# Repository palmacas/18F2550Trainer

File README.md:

# PIC18F2550 Trainer

Small PCB based on a PIC18F2550, with USB connectivity. All the GPIO pins are exposed to headers. The board includes ICSP connector for programming, but the microcontroller also can be programmed with a bootloader.

---
More information:\
[PIC18F2550 Trainer [Spanish]](https://palmacas.com/pic18f2550-trainer/)

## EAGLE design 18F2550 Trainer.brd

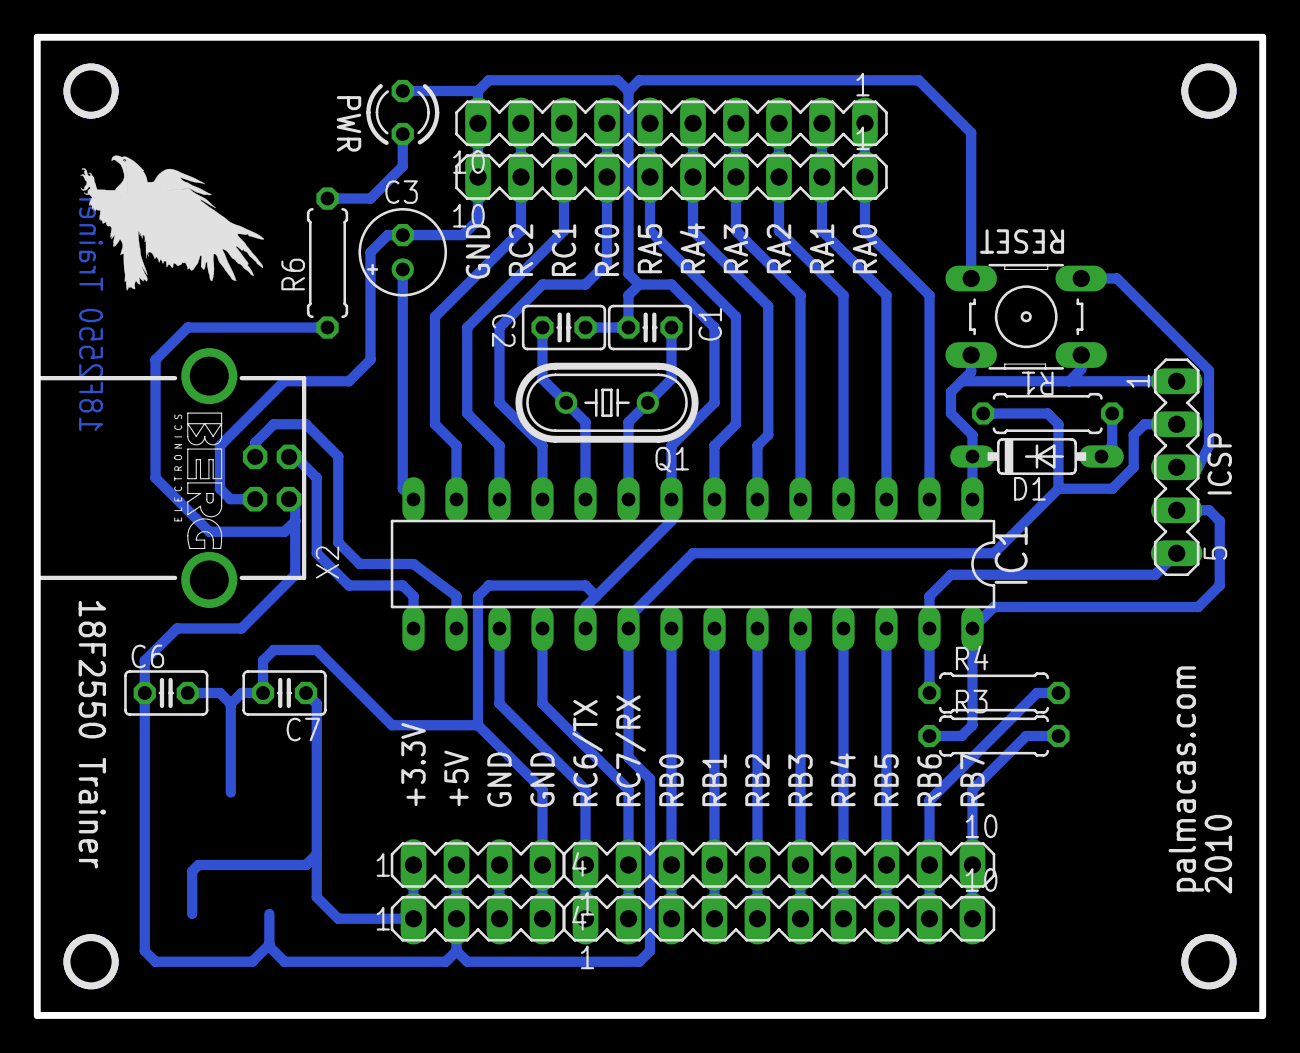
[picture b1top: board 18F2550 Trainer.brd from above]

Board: 2 copper layers, 72.4 x 57.8 mm, 25 parts (1 on the bottom side), 32 nets.

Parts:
C1, C2: 22pF; C025-025X050
C3: 47uF; E2-5
C6, C7: 1uF; C025-025X050
D1: 1N4148DO35-7; DO35-7
IC1: PIC18F2550_28DIP; DIL28-3
IC2: UA78M33; DPACK
ICSP: ICSP; MA05-1
PWR: GREEN; LED3MM
Q1: 20MHz; HC49/S
R1: 10K; 0207/7
R3, R4: 1K; 0207/7
R6: 330; 0207/7
S1: B3F-10XX
SV1, SV2, SV3, SV4: MA10-1
SV5, SV6: MA04-1
U$1: EAGLE-PLC-8MM
U$2: LOGO
X2: PN61729-S

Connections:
+3V3: C7.1, IC2.3, SV5.1, SV6.1
CLK: IC1.27, ICSP.5, R4.1
D+: IC1.16, X2.3
D-: IC1.15, X2.2
DAT: IC1.28, ICSP.4, R3.1
GND: C1.2, C2.2, C3.-, C6.2, C7.2, IC1.8, IC1.19, IC2.4, ICSP.3, PWR.K, S1.1, S1.2, SV2.10, SV3.10, SV5.3, SV5.4, SV6.3, SV6.4, X2.4
unnamed: C3.+, IC1.14
unnamed: D1.A, R1.1
unnamed: PWR.A, R6.1
OSC1: C1.1, IC1.9, Q1.1
OSC2: C2.1, IC1.10, Q1.2
RA0: IC1.2, SV2.1, SV3.1
RA1: IC1.3, SV2.2, SV3.2
RA2: IC1.4, SV2.3, SV3.3
RA3: IC1.5, SV2.4, SV3.4
RA4: IC1.6, SV2.5, SV3.5
RA5: IC1.7, SV2.6, SV3.6
RB0: IC1.21, SV1.3, SV4.3
RB1: IC1.22, SV1.4, SV4.4
RB2: IC1.23, SV1.5, SV4.5
RB3: IC1.24, SV1.6, SV4.6
RB4: IC1.25, SV1.7, SV4.7
RB5: IC1.26, SV1.8, SV4.8
RB6: R4.2, SV1.9, SV4.9
RB7: R3.2, SV1.10, SV4.10
RC0: IC1.11, SV2.7, SV3.7
RC1: IC1.12, SV2.8, SV3.8
RC2: IC1.13, SV2.9, SV3.9
RC6/TX: IC1.17, SV1.1, SV4.1
RC7/RX: IC1.18, SV1.2, SV4.2
VDD: C6.1, IC1.20, IC2.1, ICSP.2, R1.2, R6.2, SV5.2, SV6.2, X2.1
VPP: D1.C, IC1.1, ICSP.1, S1.3, S1.4

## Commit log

2020-06-03 Update LICENSE
